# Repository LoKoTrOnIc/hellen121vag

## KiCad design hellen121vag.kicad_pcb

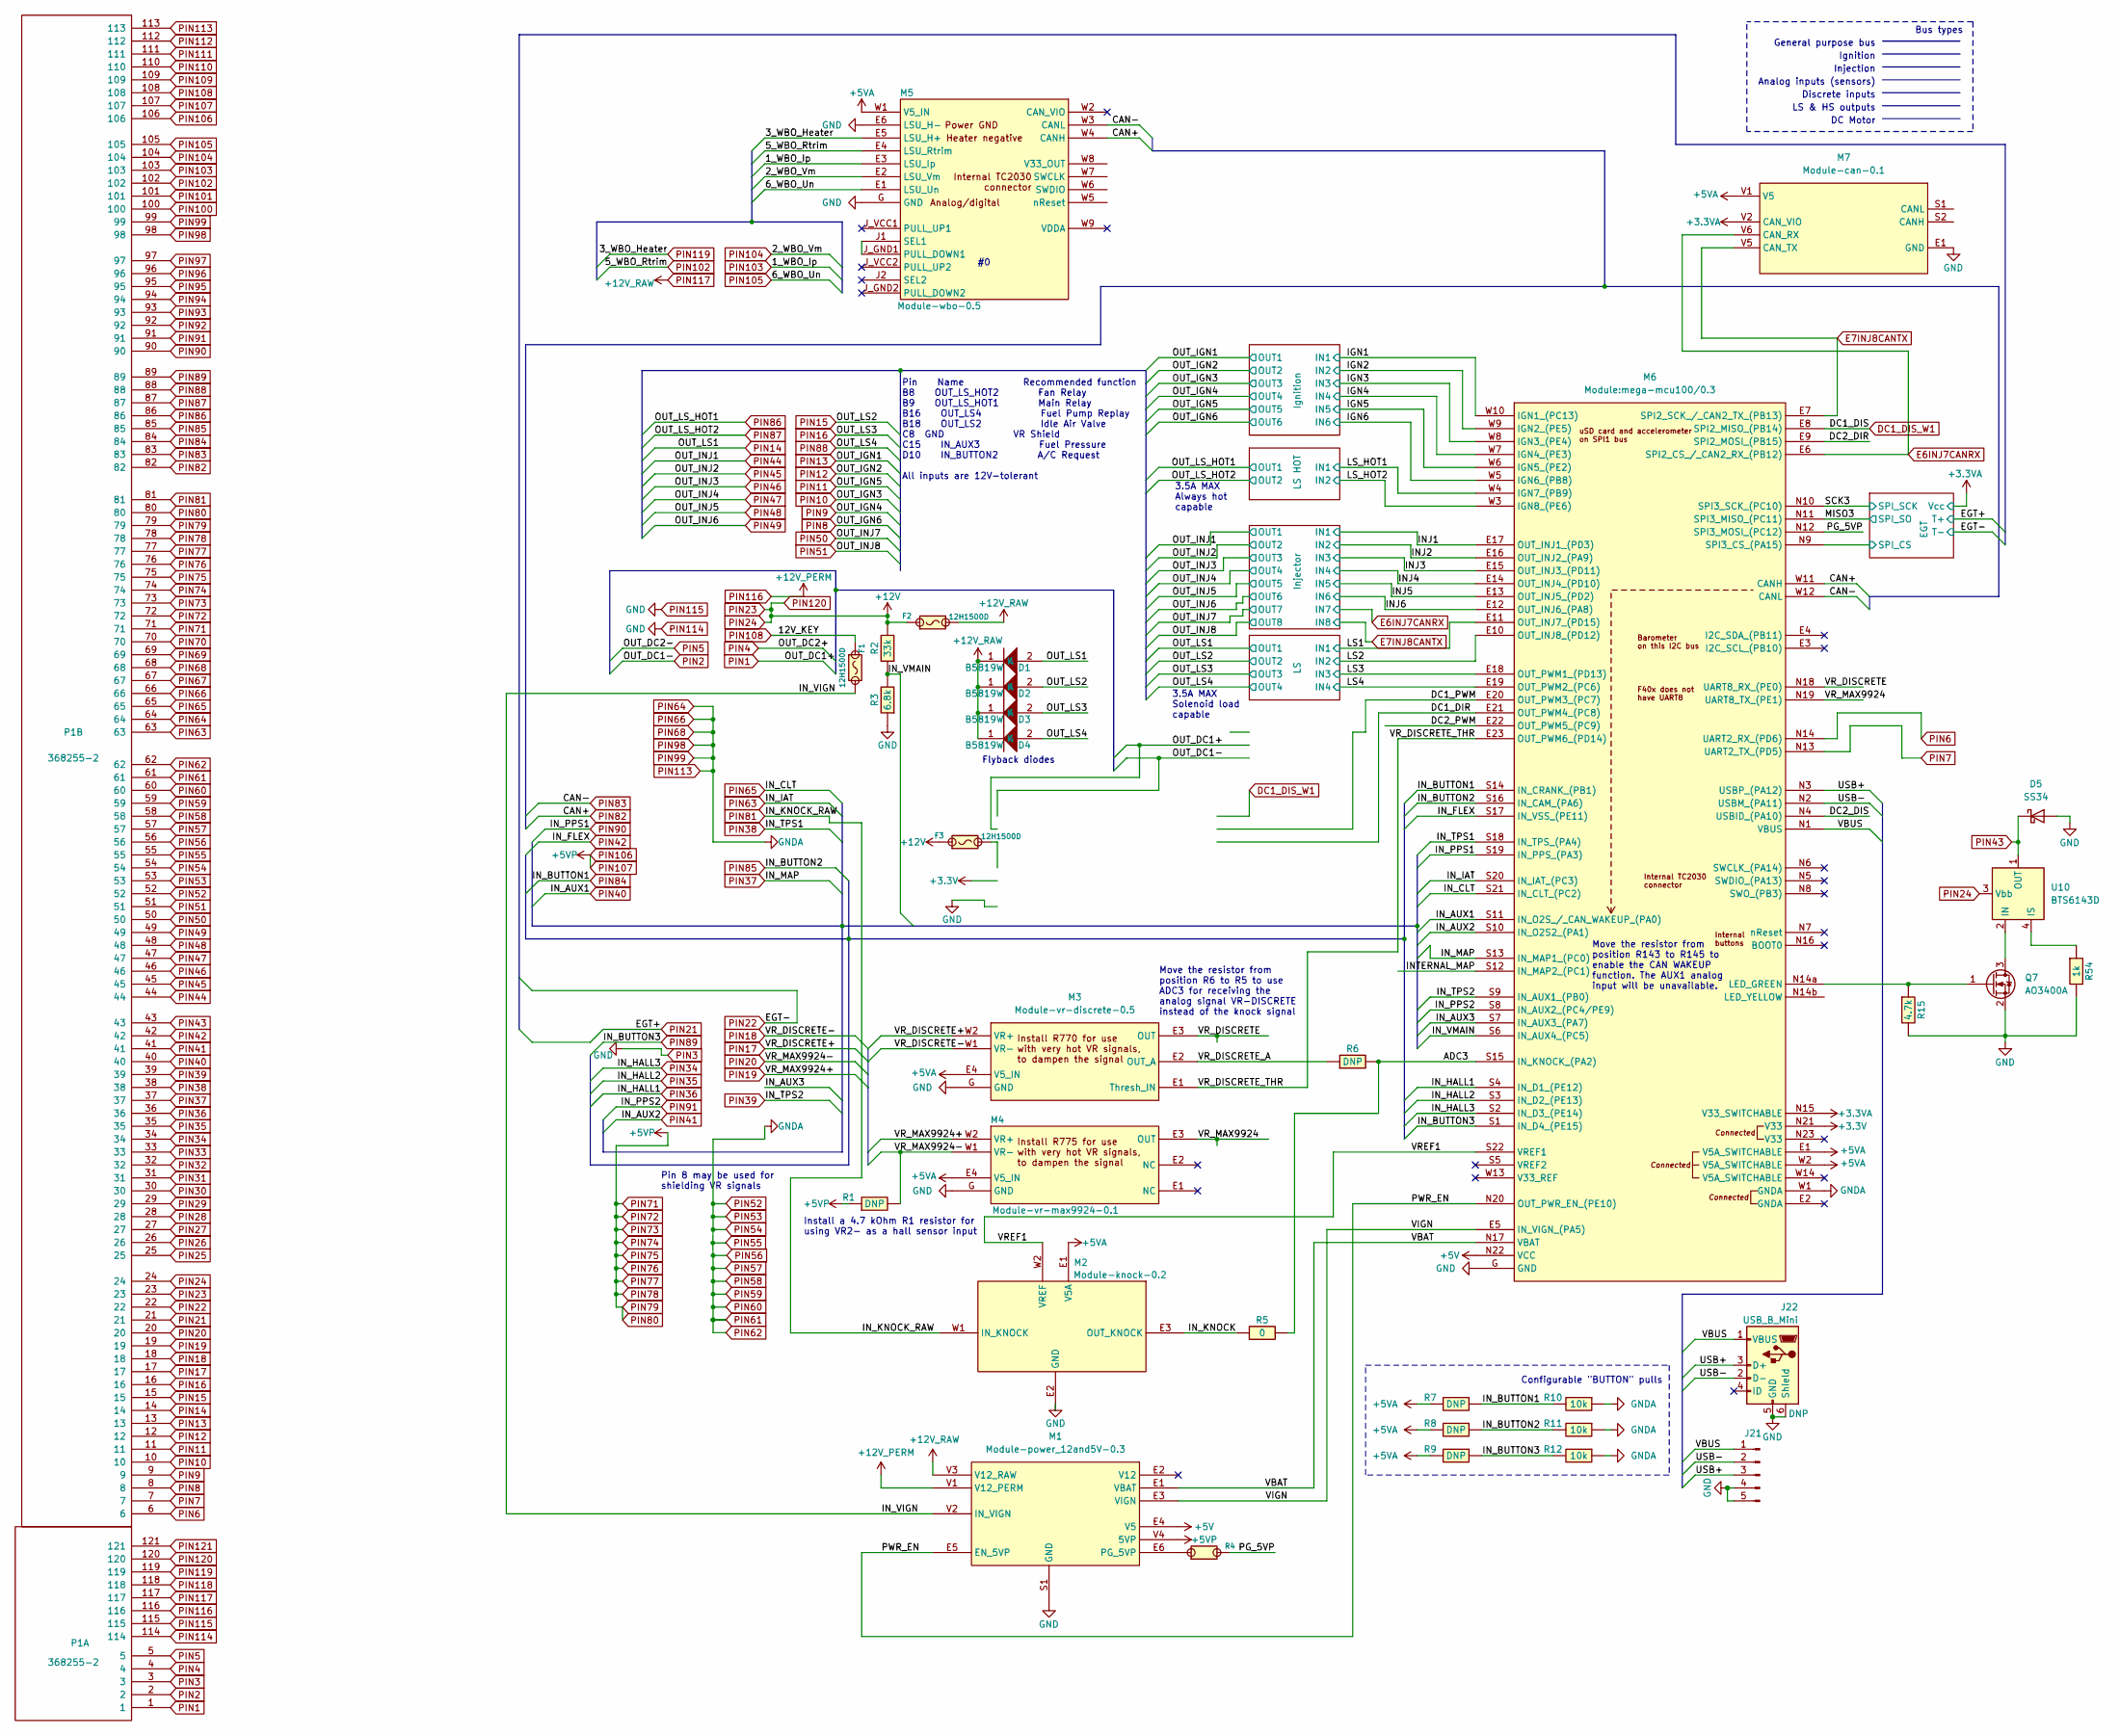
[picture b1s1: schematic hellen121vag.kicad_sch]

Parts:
D1, D2, D3, D4: B5819W; SOD-123; LCSC C8598
D5: SS34; D_SMA
F1, F2, F3: 12H1500D; PAD-1206-PAD; LCSC C182446
J21: Conn_01x05_Male; Molex_SPOX_5267-05A_1x05_P2.50mm_Vertical
J22: USB_B_Mini; USB-MINI-B-VERTICAL
M1: Module-power_12and5V-0.3; power_12and5V
M2: Module-knock-0.2; knock
M3: Module-vr-discrete-0.5; vr-discrete
M4: Module-vr-max9924-0.1; vr-max9924
M5: Module-wbo-0.5; wbo
M6: Module:mega-mcu100/0.3; mega-mcu100
M7: Module-can-0.1; can
P1: 368255-2
Q7: AO3400A; SOT-23
R1: 4.7k; R0603
R2: 33k; R0603; LCSC C4216
R3: 6.8k; R0603; LCSC C23212
R4: Jumper-Pad-Pad; PAD-0805-PAD; LCSC C17477
R5: 0; R0603; LCSC C21189
R6: 0; R0603
R7, R8, R9: DNP; R0805
R10, R11, R12: 10k; R0805; LCSC C17414
R15: 4.7k; R0603; LCSC C21189
R54: 1k; R0603; LCSC C21189
U10: BTS6143D; TO-252-4

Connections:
+3.3V: M6.N21 (V33); also elsewhere on the board
+3.3VA: M6.N15 (V33_SWITCHABLE), M7.V2 (CAN_VIO); also elsewhere on the board
+5V: M1.E4 (V5), M6.N22 (VCC)
+5VA: M2.E1 (V5A), M3.E4 (V5_IN), M4.E4 (V5_IN), M5.W1 (V5_IN), M6.E1 (V5A_SWITCHABLE), M6.W2 (V5A_SWITCHABLE), M7.V1 (V5), R7.2, R8.2, R9.2
/ADC3: M6.S15 (IN_KNOCK_(PA2)), R5.2, R6.2
/DC1_DIR: M6.E21 (OUT_PWM4_(PC8)); also elsewhere on the board
/DC1_PWM: M6.E20 (OUT_PWM3_(PC7)); also elsewhere on the board
/DC2_DIR: M6.E9 (SPI2_MOSI_(PB15))
/DC2_DIS: M6.N4 (USBID_(PA10))
/DC2_PWM: M6.E22 (OUT_PWM5_(PC9))
/EGT/SPI_CS: M6.N9 (SPI3_CS_(PA15)); also elsewhere on the board
/IGN1: M6.W10 (IGN1_(PC13)); also elsewhere on the board
/IGN2: M6.W9 (IGN2_(PE5)); also elsewhere on the board
/IGN3: M6.W8 (IGN3_(PE4)); also elsewhere on the board
/IGN4: M6.W7 (IGN4_(PE3)); also elsewhere on the board
/IGN5: M6.W6 (IGN5_(PE2)); also elsewhere on the board
/IGN6: M6.W5 (IGN6_(PB8)); also elsewhere on the board
/INJ1: M6.E17 (OUT_INJ1_(PD3)); also elsewhere on the board
/INJ2: M6.E16 (OUT_INJ2_(PA9)); also elsewhere on the board
/INJ3: M6.E15 (OUT_INJ3_(PD11)); also elsewhere on the board
/INJ4: M6.E14 (OUT_INJ4_(PD10)); also elsewhere on the board
/INJ5: M6.E13 (OUT_INJ5_(PD2)); also elsewhere on the board
/INJ6: M6.E12 (OUT_INJ6_(PA8)); also elsewhere on the board
/INTERNAL_MAP: M6.S12 (IN_MAP2_(PC1))
/IN_AUX3: M6.S7 (IN_AUX3_(PA7))
/IN_KNOCK: M2.E3 (OUT_KNOCK), R5.1
/IN_VIGN: F1.2, M1.V2 (IN_VIGN)
/IN_VMAIN: M6.S6 (IN_AUX4_(PC5)), R2.1, R3.2
/LS1: M6.E11 (OUT_INJ7_(PD15)); also elsewhere on the board
/LS2: M6.E10 (OUT_INJ8_(PD12)); also elsewhere on the board
/LS3: M6.E18 (OUT_PWM1_(PD13)); also elsewhere on the board
/LS4: M6.E19 (OUT_PWM2_(PC6)); also elsewhere on the board
/LS_HOT1: M6.W4 (IGN7_(PB9)); also elsewhere on the board
/LS_HOT2: M6.W3 (IGN8_(PE6)); also elsewhere on the board
/MISO3: M6.N11 (SPI3_MISO_(PC11)); also elsewhere on the board
/PG_5VP: M6.N12 (SPI3_MOSI_(PC12)), R4.2
/PWR_EN: M1.E5 (EN_5VP), M6.N20 (OUT_PWR_EN_(PE10))
/SCK3: M6.N10 (SPI3_SCK_(PC10)); also elsewhere on the board
/USB+: J21.3, J22.3 (D+), M6.N3 (USBP_(PA12))
/USB-: J21.2, J22.2 (D-), M6.N2 (USBM_(PA11))
/VBAT: M1.E1 (VBAT), M6.N17 (VBAT)
/VBUS: J21.1, J22.1 (VBUS), M6.N1 (VBUS)
/VIGN: M1.E3 (VIGN), M6.E5 (IN_VIGN_(PA5))
/VREF1: M2.W2 (VREF), M6.S22 (VREF1)
/VR_DISCRETE: M3.E3 (OUT), M6.N18 (UART8_RX_(PE0))
/VR_DISCRETE_A: M3.E2 (OUT_A), R6.1
/VR_DISCRETE_THR: M3.E1 (Thresh_IN), M6.E23 (OUT_PWM6_(PD14))
/VR_MAX9924: M4.E3 (OUT), M6.N19 (UART8_TX_(PE1))
DC1_DIS_W1: M6.E8 (SPI2_MISO_(PB14)); also elsewhere on the board
E6INJ7CANRX: M6.E6 (SPI2_CS_/_CAN2_RX_(PB12)), M7.V6 (CAN_RX); also elsewhere on the board
E7INJ8CANTX: M6.E7 (SPI2_SCK_/_CAN2_TX_(PB13)), M7.V5 (CAN_TX); also elsewhere on the board
unnamed 51: F3.2; also elsewhere on the board
unnamed: M1.E6 (PG_5VP), R4.1
unnamed: M5.J1 (SEL1), M5.J_GND1 (PULL_DOWN1)
unnamed: M6.N14a (LED_GREEN), Q7.1 (G), R15.1
unnamed: Q7.3 (D), U10.2 (IN)
unnamed: R54.1, U10.4 (IS)
PIN1: P1.1; also elsewhere on the board
PIN2: P1.2; also elsewhere on the board
PIN4: P1.4
PIN5: P1.5
PIN6: M6.N14 (UART2_RX_(PD6)), P1.6
PIN7: M6.N13 (UART2_TX_(PD5)), P1.7
PIN8: P1.8; also elsewhere on the board
PIN9: P1.9; also elsewhere on the board
PIN10: P1.10; also elsewhere on the board
PIN11: P1.11; also elsewhere on the board
PIN12: P1.12; also elsewhere on the board
PIN13: P1.13; also elsewhere on the board
PIN14: D1.2 (A), P1.14; also elsewhere on the board
PIN15: D2.2 (A), P1.15; also elsewhere on the board
PIN16: D3.2 (A), P1.16; also elsewhere on the board
PIN17: M3.W2 (VR+), P1.17
PIN18: M3.W1 (VR-), P1.18
PIN19: M4.W2 (VR+), P1.19
PIN20: M4.W1 (VR-), P1.20, R1.2
PIN21: P1.21; also elsewhere on the board
PIN22: P1.22; also elsewhere on the board
PIN25: P1.25
PIN26: P1.26
PIN27: P1.27
PIN28: P1.28
PIN29: P1.29
PIN30: P1.30
PIN31: P1.31
PIN32: P1.32
PIN33: P1.33
PIN34: M6.S2 (IN_D3_(PE14)), P1.34
PIN35: M6.S3 (IN_D2_(PE13)), P1.35
PIN36: M6.S4 (IN_D1_(PE12)), P1.36
PIN37: M6.S13 (IN_MAP1_(PC0)), P1.37
PIN38: M6.S18 (IN_TPS_(PA4)), P1.38
PIN39: M6.S9 (IN_AUX1_(PB0)), P1.39
PIN40: M6.S11 (IN_O2S_/_CAN_WAKEUP_(PA0)), P1.40
PIN41: M6.S10 (IN_O2S2_(PA1)), P1.41
PIN42: M6.S17 (IN_VSS_(PE11)), P1.42
PIN43: D5.1 (K), P1.43, U10.1 (OUT), U10.5 (OUT)
PIN44: P1.44; also elsewhere on the board
PIN45: P1.45; also elsewhere on the board
PIN46: P1.46; also elsewhere on the board
PIN47: P1.47; also elsewhere on the board
PIN48: P1.48; also elsewhere on the board
PIN49: P1.49; also elsewhere on the board
PIN50: P1.50; also elsewhere on the board
PIN51: P1.51; also elsewhere on the board
PIN63: M6.S20 (IN_IAT_(PC3)), P1.63
PIN65: M6.S21 (IN_CLT_(PC2)), P1.65
PIN67: P1.67
PIN69: P1.69
PIN70: P1.70
PIN81: M2.W1 (IN_KNOCK), P1.81
PIN82: M5.W4 (CANH), M6.W11 (CANH), P1.82
PIN83: M5.W3 (CANL), M6.W12 (CANL), P1.83
PIN84: M6.S14 (IN_CRANK_(PB1)), P1.84, R7.1, R10.2
PIN85: M6.S16 (IN_CAM_(PA6)), P1.85, R8.1, R11.2
PIN86: P1.86; also elsewhere on the board
PIN87: P1.87; also elsewhere on the board
PIN88: D4.2 (A), P1.88; also elsewhere on the board
PIN89: M6.S1 (IN_D4_(PE15)), P1.89, R9.1, R12.2
PIN90: M6.S19 (IN_PPS_(PA3)), P1.90
PIN91: M6.S8 (IN_AUX2_(PC4/PE9)), P1.91
PIN92: P1.92
PIN93: P1.93
PIN94: P1.94
PIN95: P1.95
PIN96: P1.96
PIN97: P1.97
PIN100: P1.100
PIN101: P1.101
PIN102: M5.E4 (LSU_Rtrim), P1.102
PIN103: M5.E3 (LSU_Ip), P1.103
PIN104: M5.E2 (LSU_Vm), P1.104
PIN105: M5.E1 (LSU_Un), P1.105
PIN106: M1.V4 (5VP), P1.71, P1.72, P1.73, P1.74, P1.75, P1.76, P1.77, P1.78, P1.79, P1.80, P1.106, P1.107, R1.1
PIN108: F1.1, P1.108
PIN109: P1.109
PIN110: P1.110
PIN111: P1.111
PIN112: P1.112
PIN113: M6.W1 (GNDA), P1.52, P1.53, P1.54, P1.55, P1.56, P1.57, P1.58, P1.59, P1.60, P1.61, P1.62, P1.64, P1.66, P1.68, P1.98, P1.99, P1.113, R10.1, R11.1, R12.1
PIN114: D5.2 (A), J21.4, J21.5, J22.5 (GND), J22.6 (Shield), M1.S1 (GND), M2.E2 (GND), M3.G (GND), M4.G (GND), M5.E6 (LSU_H-), M5.G (GND), M6.G (GND), M7.E1 (GND), P1.3, P1.114, P1.115, Q7.2 (S), R3.1, R15.2, R54.2; also elsewhere on the board
PIN116: M1.V1 (V12_PERM), P1.116
PIN117: D1.1 (K), D2.1 (K), D3.1 (K), D4.1 (K), F2.2, M1.V3 (V12_RAW), P1.117
PIN118: P1.118
PIN119: M5.E5 (LSU_H+), P1.119
PIN120: F2.1, F3.1, P1.23, P1.24, P1.120, R2.2, U10.3 (Vbb)
PIN121: P1.121

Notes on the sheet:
Analog inputs (sensors)
Install a 4.7 kOhm R1 resistor for using VR2- as a hall sensor input
Injection
Pin Name Recommended function B8 OUT_LS_HOT2 Fan Relay B9 OUT_LS_HOT1 Main Relay B16 OUT_LS4 Fuel Pump Replay B18 OUT_LS2 Idle Air Valve C8 GND VR Shield C15 IN_AUX3 Fuel Pressure D10 IN_BUTTON2 A/C Request All inputs are 12V-tolerant
Ignition
Move the resistor from position R143 to R145 to enable the CAN WAKEUP function. The AUX1 analog input will be unavailable.
Flyback diodes
DC Motor
Discrete inputs
3.5A MAX Solenoid load capable
Pin 8 may be used for shielding VR signals
General purpose bus
Bus types
Configurable "BUTTON" pulls
3.5A MAX Always hot capable
LS & HS outputs
Move the resistor from position R6 to R5 to use ADC3 for receiving the analog signal VR-DISCRETE instead of the knock signal

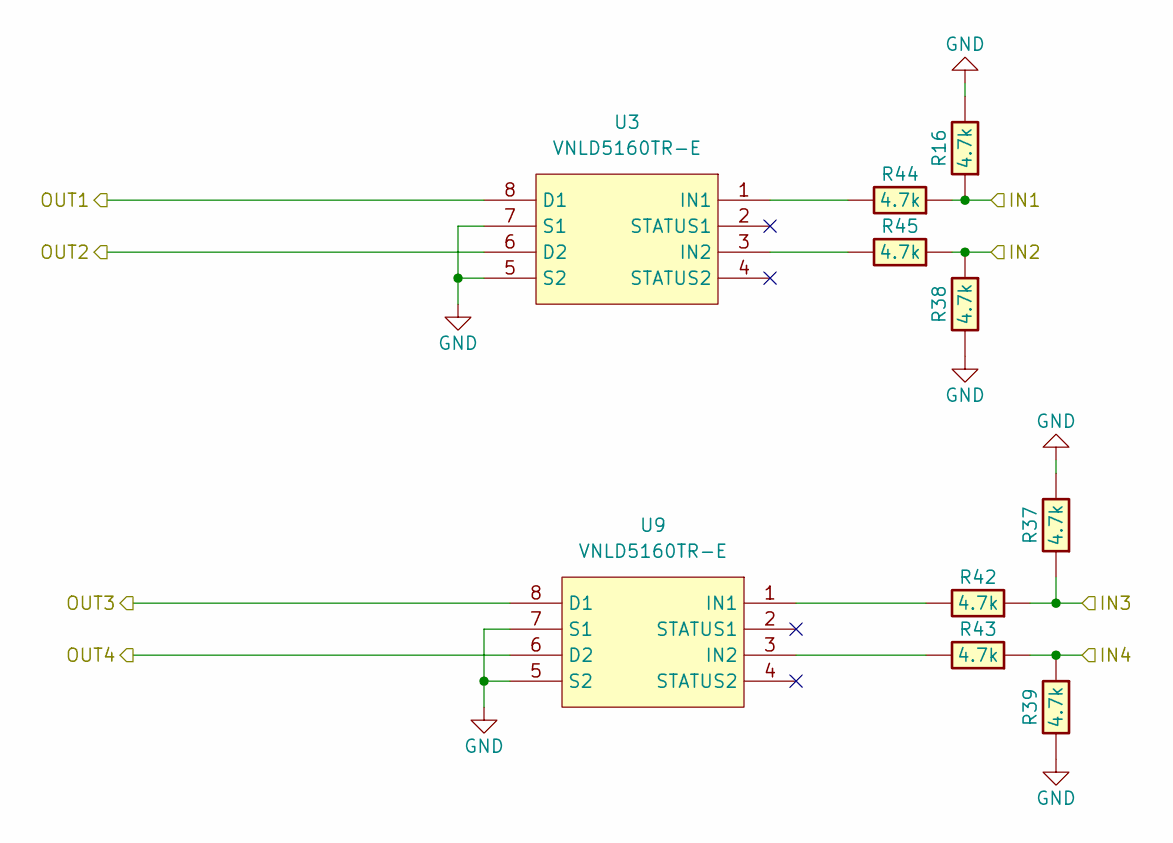
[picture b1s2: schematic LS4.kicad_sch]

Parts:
R16, R37, R38, R39, R42, R43, R44, R45: 4.7k; R0603; LCSC C23162
U3, U9: VNLD5160TR-E; SOIC-8_3.9x4.9mm_P1.27mm; LCSC C377942

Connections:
/LS1: R16.1, R44.1; also elsewhere on the board
/LS2: R38.1, R45.1; also elsewhere on the board
/LS3: R37.1, R42.1; also elsewhere on the board
/LS4: R39.1, R43.1; also elsewhere on the board
unnamed: R44.2, U3.1 (IN1)
unnamed: R45.2, U3.3 (IN2)
unnamed: R42.2, U9.1 (IN1)
unnamed: R43.2, U9.3 (IN2)
PIN14: U3.8 (D1); also elsewhere on the board
PIN15: U3.6 (D2); also elsewhere on the board
PIN16: U9.8 (D1); also elsewhere on the board
PIN88: U9.6 (D2); also elsewhere on the board
PIN114: R16.2, R37.2, R38.2, R39.2, U3.5 (S2), U3.7 (S1), U9.5 (S2), U9.7 (S1); also elsewhere on the board

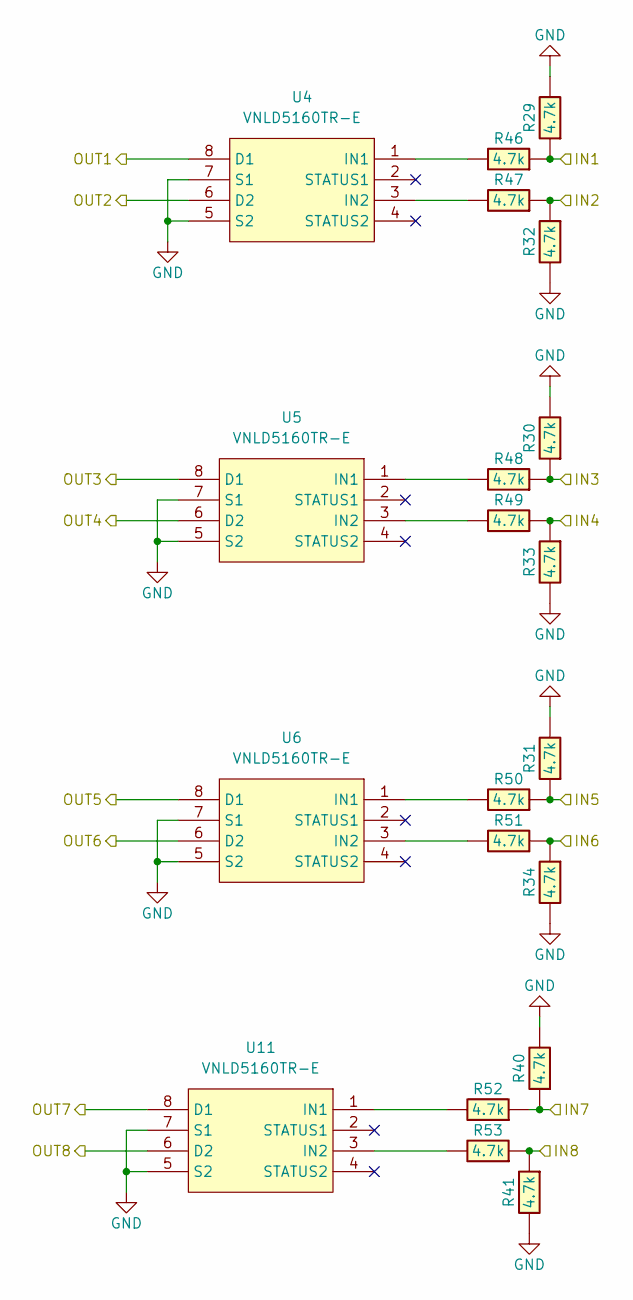
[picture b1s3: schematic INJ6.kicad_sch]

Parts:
R29, R30, R31, R32, R33, R34, R40, R41, R46, R47, R48, R49, R50, R51, R52, R53: 4.7k; R0603; LCSC C23162
U4, U5, U6, U11: VNLD5160TR-E; SOIC-8_3.9x4.9mm_P1.27mm; LCSC C377942

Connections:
/INJ1: R29.1, R46.1; also elsewhere on the board
/INJ2: R32.1, R47.1; also elsewhere on the board
/INJ3: R30.1, R48.1; also elsewhere on the board
/INJ4: R33.1, R49.1; also elsewhere on the board
/INJ5: R31.1, R50.1; also elsewhere on the board
/INJ6: R34.1, R51.1; also elsewhere on the board
E6INJ7CANRX: R40.1, R52.1; also elsewhere on the board
E7INJ8CANTX: R41.1, R53.1; also elsewhere on the board
unnamed: R46.2, U4.1 (IN1)
unnamed: R47.2, U4.3 (IN2)
unnamed: R48.2, U5.1 (IN1)
unnamed: R49.2, U5.3 (IN2)
unnamed: R50.2, U6.1 (IN1)
unnamed: R51.2, U6.3 (IN2)
unnamed: R52.2, U11.1 (IN1)
unnamed: R53.2, U11.3 (IN2)
PIN44: U4.8 (D1); also elsewhere on the board
PIN45: U4.6 (D2); also elsewhere on the board
PIN46: U5.8 (D1); also elsewhere on the board
PIN47: U5.6 (D2); also elsewhere on the board
PIN48: U6.8 (D1); also elsewhere on the board
PIN49: U6.6 (D2); also elsewhere on the board
PIN50: U11.8 (D1); also elsewhere on the board
PIN51: U11.6 (D2); also elsewhere on the board
PIN114: R29.2, R30.2, R31.2, R32.2, R33.2, R34.2, R40.2, R41.2, U4.5 (S2), U4.7 (S1), U5.5 (S2), U5.7 (S1), U6.5 (S2), U6.7 (S1), U11.5 (S2), U11.7 (S1); also elsewhere on the board

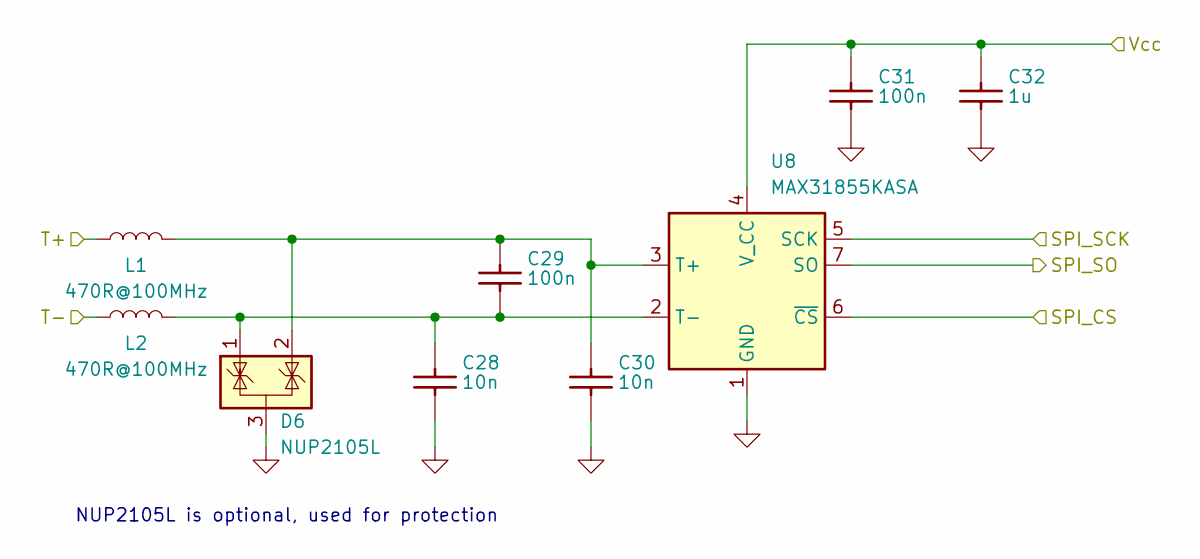
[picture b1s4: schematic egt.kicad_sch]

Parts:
C28, C30: 10n; C0603; LCSC C57112
C29, C31: 100n; C0603; LCSC C14663
C32: 1u; C0603; LCSC C15849
D6: NUP2105L; SOT-23; LCSC C284104
L1, L2: 470R@100MHz; L_0603_1608Metric; LCSC C97853
U8: MAX31855KASA; SOIC-8_3.9x4.9mm_P1.27mm; LCSC C52028

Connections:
+3.3VA: C31.2, C32.2, U8.4 (V_CC); also elsewhere on the board
/EGT/SPI_CS: U8.6 (~CS); also elsewhere on the board
/MISO3: U8.7 (SO); also elsewhere on the board
/SCK3: U8.5 (SCK); also elsewhere on the board
unnamed: C29.2, C30.2, D6.2 (K), L1.2, U8.3 (T+)
unnamed: C28.2, C29.1, D6.1 (K), L2.2, U8.2 (T-)
PIN21: L1.1; also elsewhere on the board
PIN22: L2.1; also elsewhere on the board
PIN114: C28.1, C30.1, C31.1, C32.1, D6.3 (A), U8.1 (GND); also elsewhere on the board

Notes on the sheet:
NUP2105L is optional, used for protection

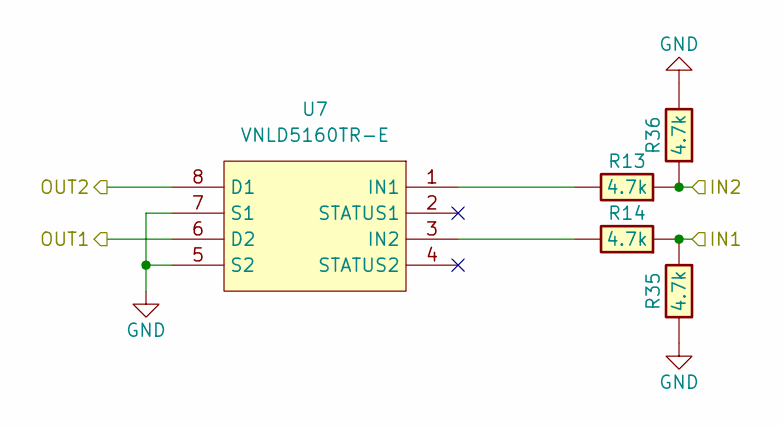
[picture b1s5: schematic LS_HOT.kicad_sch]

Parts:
R13, R14, R35, R36: 4.7k; R0603; LCSC C23162
U7: VNLD5160TR-E; SOIC-8_3.9x4.9mm_P1.27mm; LCSC C377942

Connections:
/LS_HOT1: R14.1, R35.1; also elsewhere on the board
/LS_HOT2: R13.1, R36.1; also elsewhere on the board
unnamed: R13.2, U7.1 (IN1)
unnamed: R14.2, U7.3 (IN2)
PIN86: U7.6 (D2); also elsewhere on the board
PIN87: U7.8 (D1); also elsewhere on the board
PIN114: R35.2, R36.2, U7.5 (S2), U7.7 (S1); also elsewhere on the board

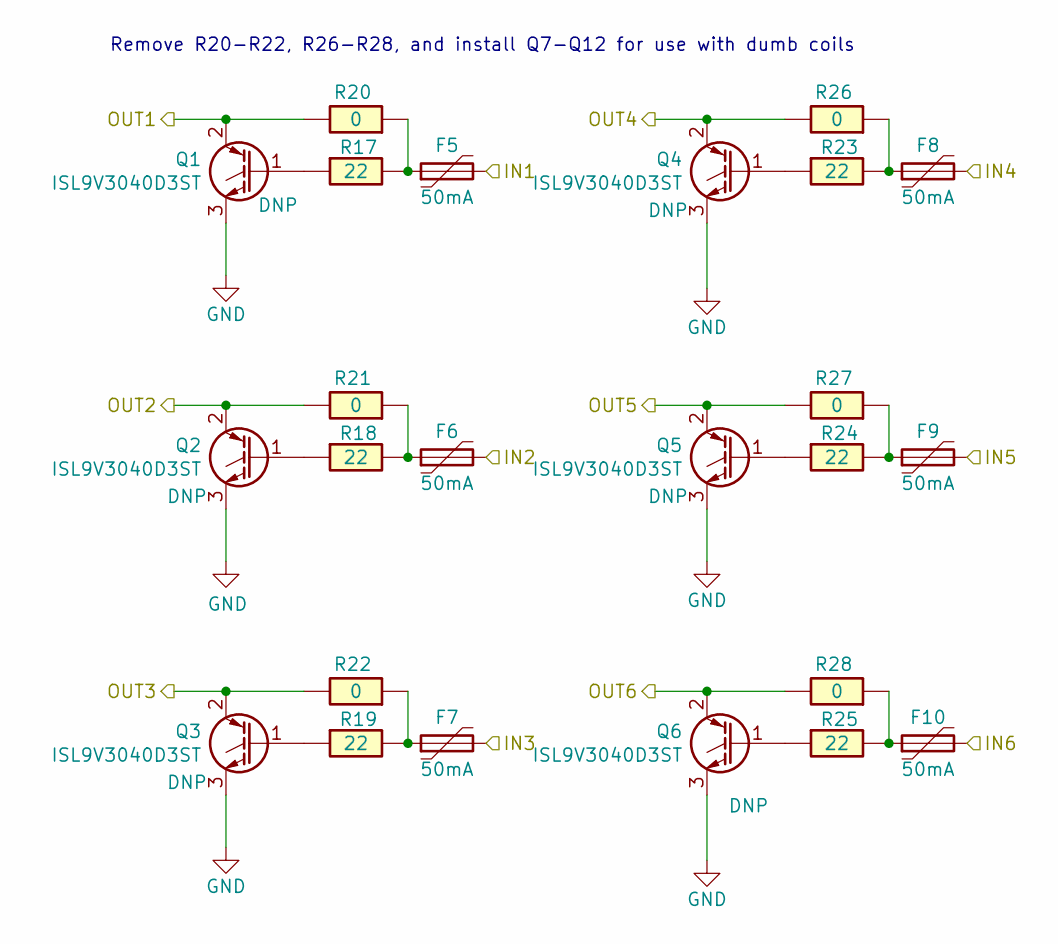
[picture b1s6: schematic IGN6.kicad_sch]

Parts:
F5, F6, F7, F8, F9, F10: 50mA; Fuse_0603_1608Metric; LCSC C369141
Q1, Q2, Q3, Q4, Q5, Q6: ISL9V3040D3ST; TO-252-2
R17, R18, R19, R23, R24, R25: 22; R0603; LCSC C23345
R20, R21, R22, R26, R27, R28: 0; R_2512_6332Metric; LCSC C25469

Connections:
/IGN1: F5.2; also elsewhere on the board
/IGN2: F6.2; also elsewhere on the board
/IGN3: F7.2; also elsewhere on the board
/IGN4: F8.2; also elsewhere on the board
/IGN5: F9.2; also elsewhere on the board
/IGN6: F10.2; also elsewhere on the board
unnamed: F5.1, R17.2, R20.1
unnamed: F6.1, R18.2, R21.1
unnamed: F7.1, R19.2, R22.1
unnamed: F8.1, R23.2, R26.1
unnamed: F9.1, R24.2, R27.1
unnamed: F10.1, R25.2, R28.1
unnamed: Q1.1 (G), R17.1
unnamed: Q2.1 (G), R18.1
unnamed: Q3.1 (G), R19.1
unnamed: Q4.1 (G), R23.1
unnamed: Q5.1 (G), R24.1
unnamed: Q6.1 (G), R25.1
PIN8: Q6.2 (C), R28.2; also elsewhere on the board
PIN9: Q4.2 (C), R26.2; also elsewhere on the board
PIN10: Q3.2 (C), R22.2; also elsewhere on the board
PIN11: Q5.2 (C), R27.2; also elsewhere on the board
PIN12: Q2.2 (C), R21.2; also elsewhere on the board
PIN13: Q1.2 (C), R20.2; also elsewhere on the board
PIN114: Q1.3 (E), Q2.3 (E), Q3.3 (E), Q4.3 (E), Q5.3 (E), Q6.3 (E); also elsewhere on the board

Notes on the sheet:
Remove R20-R22, R26-R28, and install Q7-Q12 for use with dumb coils

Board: 4 copper layers, 103 parts (52 on the bottom side), 142 nets, no tracks yet.

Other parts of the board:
M8: Module-motor-driver-0.1; motor-driver

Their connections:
+3.3V: M8.W5 (3V3_IN); also elsewhere on the board
/DC1_DIR: M8.W4 (DIR); also elsewhere on the board
/DC1_PWM: M8.W2 (PWM); also elsewhere on the board
DC1_DIS_W1: M8.W1 (DIS); also elsewhere on the board
unnamed 51: M8.N2 (12V_IN), M8.S1 (12V_IN); also elsewhere on the board
PIN1: M8.S3 (OUT+); also elsewhere on the board
PIN2: M8.S2 (OUT-); also elsewhere on the board
PIN114: M8.G (GND); also elsewhere on the board

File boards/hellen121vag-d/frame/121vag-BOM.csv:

Comment,Designator,Footprint,LCSC Part #
"VNLD5160TR-E","U11","SO8",""
"BTS6143D","U10","TO-252-4",""
"VNLD5160TR-E","U9","SO8",""
"MAX31855KASA","U8","SO8",""
"VNLD5160TR-E","U7","SO8",""
"VNLD5160TR-E","U6","SO8",""
"VNLD5160TR-E","U5","SO8",""
"VNLD5160TR-E","U4","SO8",""
"VNLD5160TR-E","U3","SO8",""
"1k","R54","R0603",""
"4.7k","R53","R0603",""
"4.7k","R52","R0603",""
"4.7k","R51","R0603",""
"4.7k","R50","R0603",""
"4.7k","R49","R0603",""
"4.7k","R48","R0603",""
"4.7k","R47","R0603",""
"4.7k","R46","R0603",""
"4.7k","R45","R0603",""
"4.7k","R44","R0603",""
"4.7k","R43","R0603",""
"4.7k","R42","R0603",""
"4.7k","R41","R0603",""
"4.7k","R40","R0603",""
"4.7k","R39","R0603",""
"4.7k","R38","R0603",""
"4.7k","R37","R0603",""
"4.7k","R36","R0603",""
"4.7k","R35","R0603",""
"4.7k","R34","R0603",""
"4.7k","R33","R0603",""
"4.7k","R32","R0603",""
"4.7k","R31","R0603",""
"4.7k","R30","R0603",""
"4.7k","R29","R0603",""
"0","R28","R2512",""
"0","R27","R2512",""
"0","R26","R2512",""
"22","R25","R0603",""
"22","R24","R0603",""
"22","R23","R0603",""
"0","R22","R2512",""
"0","R21","R2512",""
"0","R20","R2512",""
"22","R19","R0603",""
"22","R18","R0603",""
"22","R17","R0603",""
"4.7k","R16","R0603",""
"4.7k","R15","R0603",""
"4.7k","R14","R0603",""
"4.7k","R13","R0603",""
"10k","R12","R0805",""
"10k","R11","R0805",""
"10k","R10","R0805",""
"DNP","R9","R0805",""
"DNP","R8","R0805",""
"DNP","R7","R0805",""
"0","R6","R0603",""
"0","R5","R0603",""
"Jumper-Pad-Pad","R4","PAD-0805-PAD",""
"6.8k","R3","R0603",""
"33k","R2","R0603",""
"4.7k","R1","R0603",""
"AO3400A","Q7","SOT-23",""
"ISL9V3040D3ST","Q6","DPAK",""
"ISL9V3040D3ST","Q5","DPAK",""
"ISL9V3040D3ST","Q4","DPAK",""
"ISL9V3040D3ST","Q3","DPAK",""
"ISL9V3040D3ST","Q2","DPAK",""
"ISL9V3040D3ST","Q1","DPAK",""
"368255-2","P1","368255-2",""
"Module:can/0.1","M7","can",""
"Module:mega-mcu100/0.3","M6","mega-mcu100",""
"Module:wbo/0.5","M5","wbo",""
"Module:vr-max9924/0.1","M4","vr-max9924",""
"Module:vr-discrete/0.5","M3","vr-discrete",""
"Module:knock/0.2","M2","knock",""
"Module:power_12and5V/0.3","M1","power_12and5V",""
"470R@100MHz","L2","L_0603_1608Metric",""
"470R@100MHz","L1","L_0603_1608Metric",""
"USB_B_Mini","J22","USB-MINI-B-VERTICAL",""
"Conn_01x05_Male","J21","Molex_SPOX_5267-05A_1x05_P2.50mm_Vertical",""
"50mA","F10","Fuse_0603_1608Metric",""
"50mA","F9","Fuse_0603_1608Metric",""
"50mA","F8","Fuse_0603_1608Metric",""
"50mA","F7","Fuse_0603_1608Metric",""
"50mA","F6","Fuse_0603_1608Metric",""
"50mA","F5","Fuse_0603_1608Metric",""
"12H1500D","F3","PAD-1206-PAD",""
"12H1500D","F2","PAD-1206-PAD",""
"12H1500D","F1","PAD-1206-PAD",""
"NUP2105L","D6","SOT-23",""
"SS34","D5","D_SMA",""
"B5819W","D4","SOD-123",""
"B5819W","D3","SOD-123",""
"B5819W","D2","SOD-123",""
"B5819W","D1","SOD-123",""
"1u","C32","C0603",""
"100n","C31","C0603",""
"10n","C30","C0603",""
"100n","C29","C0603",""
"10n","C28","C0603",""

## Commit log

2025-12-07 modifico archive de revision
2025-12-07 [skip actions] Auto-generated board
2025-12-07 Se agrego by avelito
2025-12-08 test conexion
2025-12-08 se modifico esquema y pcb
2025-12-10 colocacion de los componentes en un 90%
2025-12-10 se ha completado un 99% la colocacion de componentes y adapatacion
2025-12-10 se hace un test de la modificacion
2025-12-10 colocacion de componentes 100%
2025-12-10 reenvio
2025-12-10 agregue el bom
2025-12-11 bom add f6
2025-12-11 fallo el bom por que faltan agregar componentes: se estan agregando los componentes segun log
2025-12-11 se agrego f10
2025-12-15 [skip actions] Auto-generated board v2.1
2025-12-17 wewe2
2025-12-17 reeeds
2025-12-17 wrqwd
2025-12-17 errfs
